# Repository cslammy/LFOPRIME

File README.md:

# LFOPRIME
Low Frequency Oscillator without a bunch of useless frills

For more information about this project, please see this blog post:
http://audiodiwhy.blogspot.com/2021/09/lfo-prime-reverse-engineering-my-own.html

In 2002 or so I designed a simple analog LFO for modular synth and desktop bench use. I never documented anything about it, but used it for several years.  
I reverse engineered my own work so here is what I ended up with.  The zip file is the gerber, for PAIA FRAC +15/-15.  
It can pretty easily be redone for SKIFF/Euro and +/- 12V, which I may attempt at some point.

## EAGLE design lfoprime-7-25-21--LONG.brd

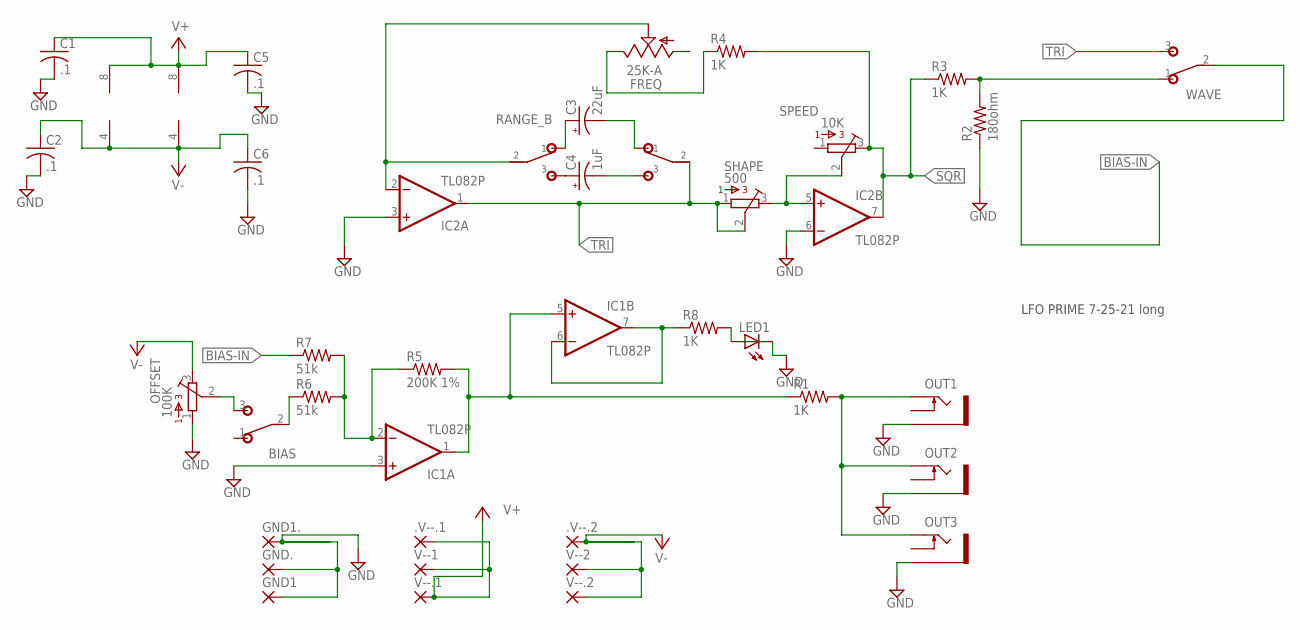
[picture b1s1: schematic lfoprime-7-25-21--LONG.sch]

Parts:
.V--.1, .V--.2: 3,17/1,3
BIAS: SPDTPADS; SPDT
C1, C2, C5, C6: .1; C025-025X050
C3: 22uF; E5-4
C4: 1uF; E5-4
FREQ: 25K-A; 9MM_SNAP-IN_POT
GND1, GND1., GND.: 3,17/1,3
IC1, IC2: TL082P; DIL08
LED1: LED3MM
OFFSET: 100K; 3362H
OUT1, OUT2, OUT3: THONKICONNNEW; WQP-PJ301M-12_JACK
R1, R3, R4, R8: 1K; 0204/7
R2: 180ohm; 0204/7
R5: 200K 1%; 0204/7
R6, R7: 51k; 0204/7
RANGE: DPDT-WIDE
SHAPE: 500; 3362H
SPEED: 10K; 3362H
V--1, V--2, V--.1, V--.2: 3,17/1,3
WAVE: SPDTPADS; SPDT

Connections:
BIAS-IN: R7.1, WAVE.2
BIAS-OUT: IC1.1 (OUT), IC1.5 (+IN), R1.1, R5.2
GND: C1.2, C2.2, C5.2, C6.2, GND1.1, GND1..1, GND..1, IC1.3 (+IN), IC2.3 (+IN), IC2.6 (-IN), LED1.K (C), OFFSET.1, OUT1.P$3_SLEEVE (SLEEVE), OUT2.P$3_SLEEVE (SLEEVE), OUT3.P$3_SLEEVE (SLEEVE), R2.1
unnamed: C4.+, RANGE.A3 (3)
unnamed: C4.-, RANGE.B3 (3)
unnamed: C3.+, RANGE.A1 (1)
unnamed: C3.-, RANGE.B1 (1)
unnamed: FREQ.2 (S), IC2.2 (-IN), RANGE.A2 (2)
unnamed: BIAS.3 (S), OFFSET.2
unnamed: IC2.5 (+IN), SHAPE.3, SPEED.2
unnamed: IC1.2 (-IN), R5.1, R6.2, R7.2
unnamed: IC1.6 (-IN), IC1.7 (OUT), R8.1
unnamed: OUT1.P$1_TIP (TIP), OUT2.P$1_TIP (TIP), OUT3.P$1_TIP (TIP), R1.2
unnamed: FREQ.3 (E), R4.1
unnamed: LED1.A, R8.2
unnamed: R2.2, R3.2, WAVE.1 (O)
unnamed: BIAS.2, R6.1
SQR: IC2.7 (OUT), R3.1, R4.2, SPEED.3
TRI: IC2.1 (OUT), RANGE.B2 (2), SHAPE.1, SHAPE.2, WAVE.3 (S)
V+: .V--.1.1, C1.1, C5.1, IC1.8 (V+), IC2.8 (V+), V--1.1, V--.1.1
V-: .V--.2.1, C2.1, C6.1, IC1.4 (V-), IC2.4 (V-), OFFSET.3, V--2.1, V--.2.1

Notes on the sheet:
LFO PRIME 7-25-21 long

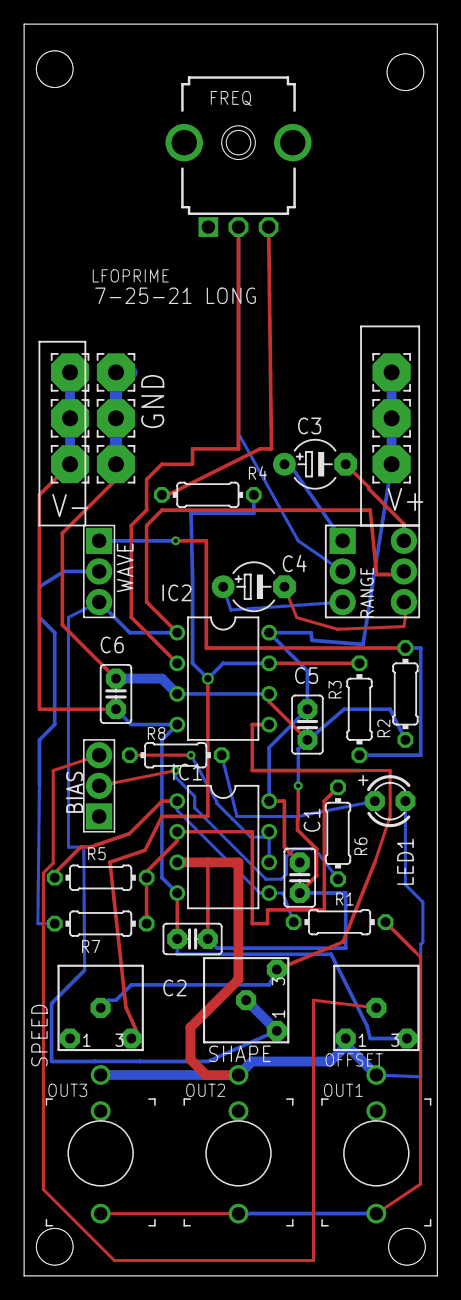
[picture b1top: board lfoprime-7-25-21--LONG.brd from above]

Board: 2 copper layers, 34.3 x 103.8 mm, 36 parts (0 on the bottom side), 21 nets.

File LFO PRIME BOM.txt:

Part   Value         Device           Package            Description                                        
 

C1     .1   25V         C-US025-025X050  C025-025X050       CAPACITOR, American symbol                                                                                              
C2     .1     25V       C-US025-025X050  C025-025X050       CAPACITOR, American symbol                                                                                              
C3     22uF     25V     CPOL-USE5-4      E5-4               POLARIZED CAPACITOR, American symbol                                                                                    
C4     1uF        25V   CPOL-USE5-4      E5-4               POLARIZED CAPACITOR, American symbol                                                                                    
C5     .1        25V    C-US025-025X050  C025-025X050       CAPACITOR, American symbol                                                                                              
C6     .1         25V    C-US025-025X050  C025-025X050       CAPACITOR, American symbol                                                                                              
FREQ   A25K          9MM_SNAP-IN_POT_ 9MM_SNAP-IN_POT    9mm vertical snap-in pot, Alpha / Panasonic style   .  One of these works.   
https://www.taydaelectronics.com/25k-ohm-linear-taper-potent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                                                                
 
IC1    TL082P        TL082P           DIL08              OP AMP                                              
IC2    TL082P        TL082P           DIL08              OP  AMP
LED1                 LED3MM           LED3MM             LED       (optional, any 3mm LED will work)                                                                                                              
OFFSET 100K          3362H            3362H              3362 Series  single turn 100K trim                                                                                                     
OUT1   THONKICONNNEW THONKICONNNEW    WQP-PJ301M-12_JACK 3.5mm socket for Eurorack modular synths                                                                                
OUT2   THONKICONNNEW THONKICONNNEW    WQP-PJ301M-12_JACK 3.5mm socket for Eurorack modular synths                                                                                
OUT3   THONKICONNNEW THONKICONNNEW    WQP-PJ301M-12_JACK 3.5mm socket for Eurorack modular synths      
resistors are 5% 1/4 watt through hole.                                                                          
R1     1K            R-US_0204/7      0204/7             RESISTOR, American symbol                                                                                               
R2     180ohm        R-US_0204/7      0204/7             RESISTOR, American symbol                                                                                               
R3     1K            R-US_0204/7      0204/7             RESISTOR, American symbol                                                                                               
R4     1K            R-US_0204/7      0204/7             RESISTOR, American symbol                                                                                               
R5     200K 1%       R-US_0204/7      0204/7             RESISTOR, American symbol                                                                                               
R6     50K           R-US_0204/7      0204/7             RESISTOR, American symbol                                                                                               
R7     50K           R-US_0204/7      0204/7             RESISTOR, American symbol                                                                                               
R8     1K            R-US_0204/7      0204/7             RESISTOR, American symbol        
Trimmer are bournes or bournes clones.                                                                                       
SHAPE  500           3362H            3362H              3362 Series  500ohm single turn trimmer                                                                                                       
SPEED  10K           3362H            3362H              3362 Series       10K single turn trimmer     
OFFSET 100K   3362H                                         3362 Series  100K single turn trimmer                                                                                                  

================
Switches: make sure to get ones that fit the PCB layout.
You will need 2x submini SPDT switches and 1x DPDT.
Here is what I used (current 9-13-21)
 
BIAS                 SPDTPADS         SPDT               TOGGLE SWITCH                                                                                                                                                                                                         
(and)
WAVE                 SPDTPADS         SPDT               TOGGLE SWITCH      https://m.made-in-china.com/product/for-Audio-Products-Spdt-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       (or)
https://lovemyswitches.com/taiway-spdt-on-on-switch-pcb-long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                                                                                                 
RANGE                DPDT-WIDE        DPDT-WIDE    TAIWAY T2 submini DPDT pcb switch ; something like this.    
https://lovemyswitches.com/taiway-dpdt-on-on-switch-pcb-moun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

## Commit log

2021-09-13 Initial upload of files
    Please see the blog post at http://audiodiwhy.blogspot.com/2021/09/lfo-prime-reverse-engineering-my-own.html for detail.
2021-12-27 Basic Details about project, initial upload
